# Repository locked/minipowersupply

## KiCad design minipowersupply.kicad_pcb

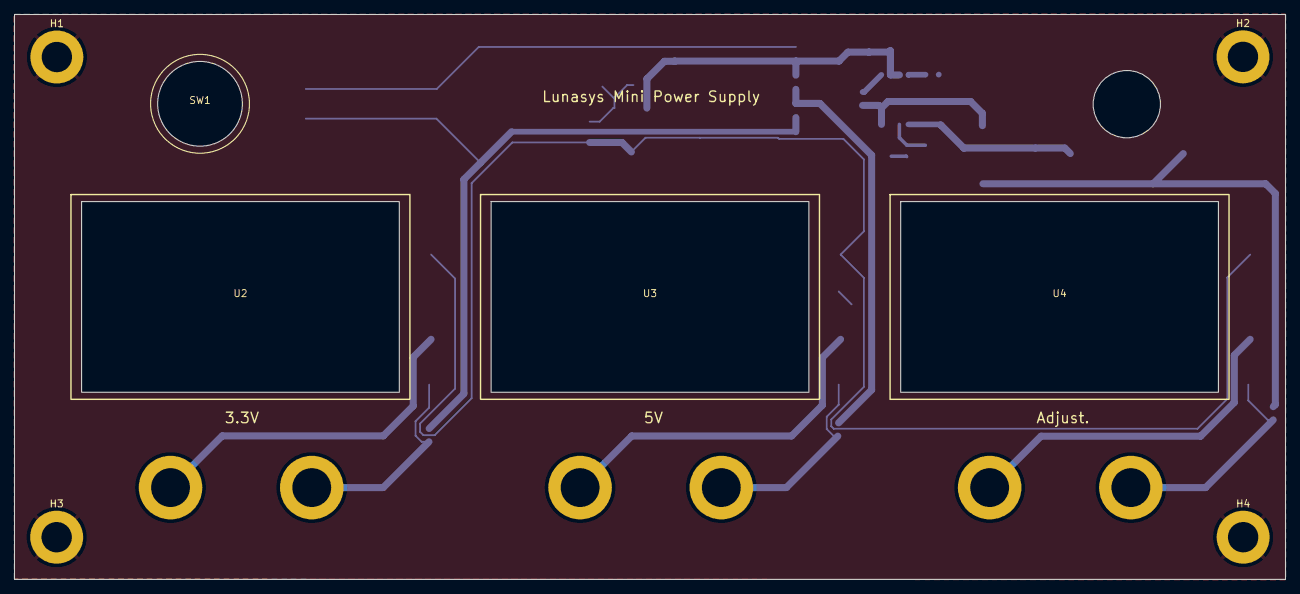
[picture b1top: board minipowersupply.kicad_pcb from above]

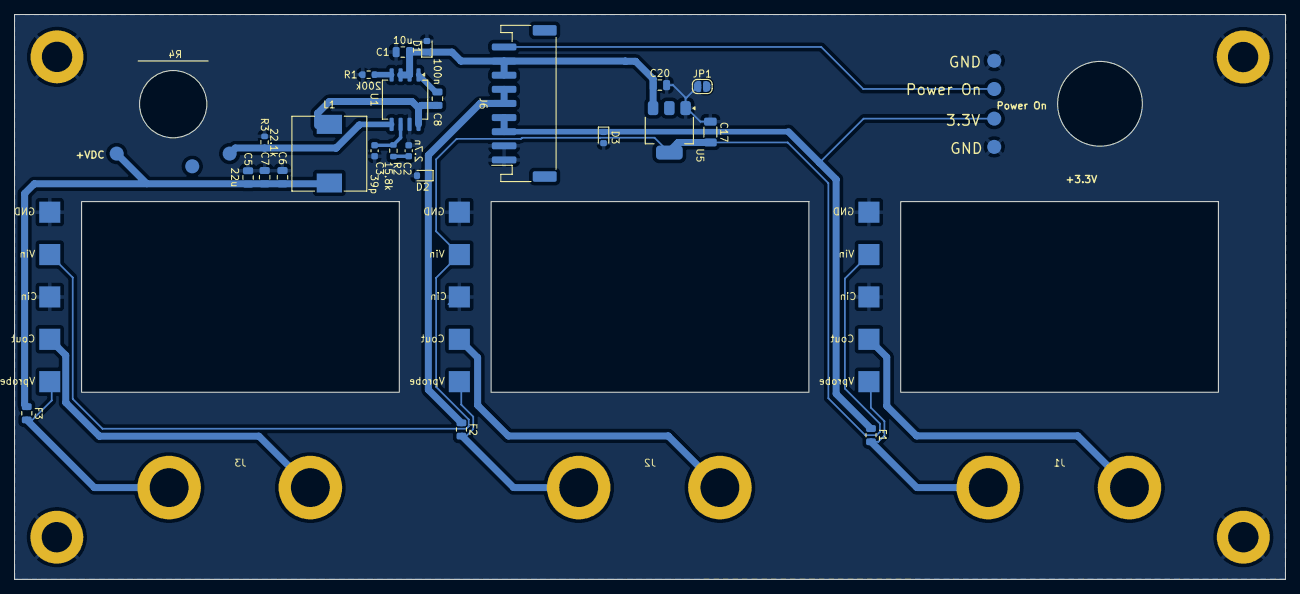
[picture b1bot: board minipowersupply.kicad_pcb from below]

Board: 2 copper layers, 180.0 x 80.0 mm, 35 parts (23 on the bottom side), 19 nets.

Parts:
C1, C20: 10u; C_0805_2012Metric
C2: 2.7n; C_0603_1608Metric
C3: 39p; C_0603_1608Metric
C5, C6, C7: 22u; C_0805_2012Metric
C8: 100n; C_0805_2012Metric
C17: 10u; C_1206_3216Metric
D1, D2, D3: D_0603_1608Metric
F1, F2, F3: Polyfuse; Fuse_0805_2012Metric
H1, H2, H3, H4: MountingHole; MountingHole_4.3mm_M4_DIN965_Pad
J1: 3.3V; banana_connector
J2: 5V; banana_connector
J3: AdjustV; banana_connector
J6: JST-PH2 Bat; JST_PH_S9B-PH-SM4-TB_1x09-1MP_P2.00mm_Horizontal
JP1: SolderJumper_2_Open; SolderJumper-2_P1.3mm_Open_RoundedPad1.0x1.5mm
L1: 3.6uH; L_10.4x10.4_H4.8
R1: 200k; R_0603_1608Metric
R2: 15.8k; R_0603_1608Metric
R3: 22.1k; R_0603_1608Metric
R4: 115k; Potentiometer_Bourns_PDB181-GTR01_Vertical
SW1: SW_MEC_5G_LED; pushbutton
U1: AP64500SP-13; SO-8_5.3x6.2mm_P1.27mm
U2, U3, U4: Voltmeter
U5: NCP1117-5_SOT223; SOT-223-3_TabPin2

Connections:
3.3V: D3.1 (A1), F1.1, J6.3, J6.4, SW1.3 (K)
5V: D2.1 (A1), F2.1, J6.5, J6.6
12V: C1.1, C20.1, D1.1 (A1), J6.7, J6.8, U1.2 (VIN), U1.3 (EN), U5.3 (VI)
+VDC: C5.1, C6.1, C7.1, F3.1, L1.2, R4.2
unnamed: C2.1, R2.2
unnamed: J1.1, U2.4 (Cout)
unnamed: F1.2, J1.2, U2.5 (Vprobe)
unnamed: J2.1, U3.4 (Cout)
unnamed: F2.2, J2.2, U3.5 (Vprobe)
unnamed: J3.1, U4.4 (Cout)
unnamed: F3.2, J3.2, U4.5 (Vprobe)
unnamed: C8.1, U1.1 (BST)
unnamed: C3.1, R2.1, U1.6 (COMP)
unnamed: R3.1, R4.1, U1.5 (FB)
unnamed: R1.1, U1.4 (RT/CLK)
unnamed: C8.2, L1.1, U1.8 (SW)
Power On: J6.9, SW1.4 (A)
Volt-5V: C17.1, U2.2 (Vin), U3.2 (Vin), U4.2 (Vin), U5.2 (VO)
Volt-GND: C1.2, C2.2, C3.2, C5.2, C6.2, C7.2, C17.2, C20.2, D1.2 (A2), D2.2 (A2), D3.2 (A2), H1.1, H2.1, H3.1, H4.1, J6.1, J6.2, JP1.1 (A), R1.2, R3.2, SW1.1, SW1.2, U1.7 (GND), U2.1 (GND), U2.3 (Cin), U3.1 (GND), U3.3 (Cin), U4.1 (GND), U4.3 (Cin), U5.1 (GND)

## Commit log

2024-08-14 initial import, lots of things to fix following first case+pcb release
2024-08-30 increase size of pads, reorganize a bit
2026-04-14 [case] add support, change screw system
2026-04-14 [pcb] misc
2026-04-14 [case] remove vents (useless)
2026-04-15 [case] add v3
2026-04-17 [case] v4: add space for pcb, add vent, fix screw place
